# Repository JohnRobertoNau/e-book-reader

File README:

Schema bloc se gaseste aici:
https://drive.google.com/drive/u/0/folders/1svHynGlwr7JKA02n5Jt7F-PYmH98pda1

BOM:

| Component                   | Quantity | Price (€) | Link                                                                                                                            | Datasheet                                                                                                                             |
| :-------------------------- | -------- | --------- | ------------------------------------------------------------------------------------------------------------------------------- | ------------------------------------------------------------------------------------------------------------------------------------- |
| W25Q512JVEIQ                | 1        | 5.84      | https://eu.mouser.com/ProductDetail/Winbond/W25Q512JVEIQ?qs=l7cgNqFNU1jw6svr3at6tA%3D%3D                                        | https://eu.mouser.com/datasheet/2/949/Winbond_W25Q512JV_Datasheet-3240039.pdf                                                         |
| MAX17048G+T10               | 1        | 4.28      | https://eu.mouser.com/ProductDetail/Analog-Devices-Maxim-Integrated/MAX17048G%2bT10?qs=D7PJwyCwLAoGnnn8jEPRBQ%3D%3D             | https://eu.mouser.com/datasheet/2/609/MAX17048_MAX17049-3469099.pdf                                                                   |
| ESP32-C6-WROOM-1-N8         | 1        | 2.97      | https://eu.mouser.com/ProductDetail/Espressif-Systems/ESP32-C6-WROOM-1-N8?qs=8Wlm6%252BaMh8ST02Gmwp74cw%3D%3D                   | https://eu.mouser.com/datasheet/2/891/Espressif_ESP32_C6_WROOM_1__Datasheet_V0_1_PRELIMI-3239987.pdf                                  |
| 112A-TAAR-R03_ATTEND        | 1        | 1.05      | https://store.comet.srl.ro/Catalogue/Product/43497/                                                                             | https://store.comet.bg/download-file.php?id=27596                                                                                     |
| QWIIC_RIGHT_ANGLE           | 1        | 3.75      | https://eu.mouser.com/ProductDetail/Adafruit/4208?qs=PzGy0jfpSMtbScLbr0L5dw%3D%3D                                               | https://cdn-shop.adafruit.com/datasheets/HX8340-B_N__DS_preliminary_v01_071203.pdf                                                    |
| BD5229G-TR                  | 1        | 0.75      | https://eu.mouser.com/ProductDetail/ROHM-Semiconductor/BD5229G-TR?qs=4kLU8WoGk0vvnhrrYwdszw%3D%3D                               | https://fscdn.rohm.com/en/products/databook/datasheet/ic/power/voltage_detector/bd52xxg-e.pdf                                         |
| 1uF capacitor               | 1        | 0.13      | https://eu.mouser.com/ProductDetail/TAIYO-YUDEN/MAASL105CC7105MFCA01?qs=HFfMDpzxxd1Fn%2FInbJA7vw%3D%3D                          | https://eu.mouser.com/datasheet/2/396/TAIYO_YUDEN_04_27_2024_c_mlcc_A_e1-3451516.pdf                                                  |
| PGB1010603MR                | 6        | 0.40      | https://eu.mouser.com/ProductDetail/Littelfuse/PGB1010603MR?qs=gu7KAQ731URLg4GSnNNN7Q%3D%3D                                     | https://www.littelfuse.com/assetdocs/pulseguard-esd-suppressors-pgb1-datasheet?assetguid=8a337998-d54d-466b-be4e-dc5bcd1f9321         |
| MCP73831                    | 1        | 0.16      | https://eu.mouser.com/ProductDetail/Microchip-Technology/MCP73831T-5ACI-OT?qs=hH%252BOa0VZEiAcgAcEkuamXg%3D%3D                  | https://eu.mouser.com/datasheet/2/268/MCP73831_Family_Data_Sheet_DS20001984H-3441711.pdf                                              |
| 200 ohm resistor            | 1        | 0.10      | https://eu.mouser.com/ProductDetail/Wurth-Elektronik/560112110211?qs=sGAEpiMZZMtlubZbdhIBIIgWRUA0vTGpVUEy0IEGMjk%3D             | https://www.we-online.com/components/products/datasheet/560112110211.pdf                                                              |
| 2k ohm resistor             | 1        | 0.57      | https://eu.mouser.com/ProductDetail/Vishay-Beyschlag/MCS04020D2321BE100?qs=sGAEpiMZZMtlubZbdhIBINHXX5XJLWKoe%2FyX%252BeuBVuo%3D | https://www.vishay.com/docs/28700/mcx0x0xpre.pdf                                                                                      |
| XC6220A331MR-G              | 1        | 1.46      | https://eu.mouser.com/ProductDetail/Torex-Semiconductor/XC6220A331MR-G?qs=AsjdqWjXhJ8ZSWznL1J0gg%3D%3D                          | https://eu.mouser.com/datasheet/2/760/xc6220-3371556.pdf                                                                              |
| 100uF tant capacitor        | 1        | 25.19     | https://eu.mouser.com/ProductDetail/Vishay-Sprague/T97F107M035HAA?qs=kE1vTINknaW2TSWjulhndg%3D%3D                               | https://www.vishay.com/docs/40092/t97.pdf                                                                                             |
| 100k resistor               | 1        | 0.30      | https://eu.mouser.com/ProductDetail/Vishay-BC-Components/NTCS0402E3104JHT?qs=8wHch9UpSvY0bmpK2FbGWQ%3D%3D                       | https://www.vishay.com/docs/29003/ntcs0402e3t.pdf                                                                                     |
| CPH3225A                    | 1        | 2.33      | https://eu.mouser.com/ProductDetail/Seiko-Semiconductors/CPH3225A?qs=3etwrb1wR%252BhUOph6lAO7eg%3D%3D                           | https://eu.mouser.com/datasheet/2/360/Seiko_Instruments_MicroBattery_E_20230330_2024Jan_-3561061.pdf                                  |
| R_CAPACITOR                 | 1        | 0.12      | https://eu.mouser.com/ProductDetail/Panasonic/ERJ-2RKD15R0X?qs=8CJXEYeWfIrWZI67d3moiA%3D%3D                                     | https://industrial.panasonic.com/cdbs/www-data/pdf/RDA0000/AOA0000C304.pdf                                                            |
| FH34SRJ-24S-0.5SH_99_       | 1        | 2.60      | https://eu.mouser.com/ProductDetail/Hirose-Connector/FH34SRJ-24S-0.5SH99?qs=vcbW%252B4%252BSTIpKBl5ap9J8Fw%3D%3D                | https://eu.mouser.com/datasheet/2/185/FH34SRJ_24S_0_5SH_99__CL0580_1255_6_99_2DDrawing_0-1615044.pdf                                  |
| 0.1uF/50V capacitor         | 1        | 0.45      | https://eu.mouser.com/ProductDetail/KYOCERA-AVX/04025C104MAT2A?qs=sGAEpiMZZMukHu%252BjC5l7YbsWA2wxb4GLrh7pRRirNkk%3D            | https://eu.mouser.com/datasheet/2/40/KGM_X7R-3223212.pdf                                                                              |
| 1uF/50V capacitor           | 10       | 0.56      | https://eu.mouser.com/ProductDetail/TAIYO-YUDEN/MAASU32NSB7105KTCA01?qs=HFfMDpzxxd06eur8w0VYhA%3D%3D                            | https://eu.mouser.com/datasheet/2/396/TDK_4_24_2024_MAASU32NSB7105KTCA01_SS-3440852.pdf                                               |
| 2k ohm resistor             | 1        | 0.57      | https://eu.mouser.com/ProductDetail/Vishay-Beyschlag/MCS04020D2321BE100?qs=sGAEpiMZZMtlubZbdhIBINHXX5XJLWKoe%2FyX%252BeuBVuo%3D | https://www.vishay.com/docs/28700/mcx0x0xpre.pdf                                                                                      |
| BME688                      | 1        | 14.82     | https://eu.mouser.com/ProductDetail/Bosch-Sensortec/BME680-Shuttle-Board-3.0?qs=Wj%2FVkw3K%252BMABg5lm5143Ww%3D%3D              | https://eu.mouser.com/datasheet/2/783/bst_bme680_sf000-2486508.pdf                                                                    |
| 2.2 ohm resistor            | 1        | 0.15      | https://eu.mouser.com/ProductDetail/Panasonic/ERJ-PA2J2R2X?qs=sGAEpiMZZMtlubZbdhIBIKn8wLs5z3UnO%252BN6Zqj8Y2A%3D                | https://industrial.panasonic.com/cdbs/www-data/pdf/RDO0000/AOA0000C331.pdf                                                            |
| MBR0530                     | 3        | 0.18      | https://eu.mouser.com/ProductDetail/onsemi/MBR0530T3G?qs=3JMERSakebpEmdUS6GetdQ%3D%3D                                           | https://www.onsemi.com/download/data-sheet/pdf/mbr0530t1-d.pdf                                                                        |
| SI1308EDL-T1-GE3            | 1        | 0.42      | https://eu.mouser.com/ProductDetail/Vishay-Semiconductors/SI1308EDL-T1-GE3?qs=bX1%252BNvsK%2FBramh9tgpOaEw%3D%3D                | https://www.vishay.com/docs/63399/si1308edl.pdf                                                                                       |
| 0.47 ohm resistor           | 1        | 0.61      | https://eu.mouser.com/ProductDetail/ROHM-Semiconductor/UCR01MVPFLR470?qs=493kPxzlxfJor42A3tTE6g%3D%3D                           | https://fscdn.rohm.com/en/products/databook/datasheet/passive/resistor/chip_resistor/ucr-e.pdf                                        |
| 4.7uF/25V capacitor         | 1        | 0.27      | https://eu.mouser.com/ProductDetail/KYOCERA-AVX/04023D475MAT2A?qs=sGAEpiMZZMsh%252B1woXyUXj%252BCoURFk43JpehNp%2F1Fl9pk%3D      | https://eu.mouser.com/datasheet/2/40/cx5r-2835979.pdf                                                                                 |
| 68uH ind                    | 1        | 1.37      | https://store.comet.srl.ro/CatalogueFarnell/Product/1302649/                                                                    | https://www.we-online.com/components/products/datasheet/744043680.pdf                                                                 |
| 10uF capacitor              | 1        | 0.28      | https://eu.mouser.com/ProductDetail/KYOCERA-AVX/KGM05CS60J106MH?qs=9vOqFld9vZXSfhl2b2Q2gQ%3D%3D                                 | https://eu.mouser.com/datasheet/2/40/KGM_X6S-3223173.pdf                                                                              |
| SAMACSYS_PARTS_USB4110-GF-A | 1        | 1.18      | https://eu.mouser.com/ProductDetail/GCT/USB4110-GF-A?qs=KUoIvG%2F9IlYiZvIXQjyJeA%3D%3D                                          | https://eu.mouser.com/datasheet/2/837/GCT_USB4110_Product_Drawing___20k_cycles-3455479.pdf                                            |
| PFMF.050.1                  | 1        | 0.28      | https://eu.mouser.com/ProductDetail/Schurter/PFMF.050.2?qs=1auRipcfynCums5v1iucSA%3D%3D                                         | https://eu.mouser.com/datasheet/2/358/typ_PFMF-1275918.pdf                                                                            |
| 5k1 resistor                | 2        | 0.15      | https://eu.mouser.com/ProductDetail/Vishay-Beyschlag/MCS04020C5101FE000?qs=sGAEpiMZZMtlubZbdhIBIMAhWB6%252BRofmP3o4x7R7qwI%3D   | https://www.vishay.com/docs/28705/mcx0x0xpro.pdf                                                                                      |
| Battery                     | 1        | 10.45     | https://www.emag.ro/acumulator-li-polymer-2500mah-3-7v-104050-243/pd/D6VB6SMBM/                                                 | https://www.ufinebattery.com/images/upload/ufx0165-11-3-7v-2500mah-lithium-ion-battery-product-datasheet.pdf                          |
| Display                     | 1        | 44.12     | https://www.waveshare.com/7.5inch-e-paper.htm                                                                                   | https://files.waveshare.com/upload/6/60/7.5inch_e-Paper_V2_Specification.pdf                                                          |
| 100nF capacitor             | 8        | 0.013     | https://store.comet.srl.ro/Catalogue/Product/48939/                                                                             | https://store.comet.bg/download-file.php?id=11                                                                                        |
| 10k resistor                | 16       | 0.19      | https://eu.mouser.com/ProductDetail/Vishay/MCS04020D1022BE000?qs=pUKx8fyJudATYWOpd0Fc%2FA%3D%3D                                 | https://www.vishay.com/docs/28700/mcx0x0xpre.pdf                                                                                      |
| 4.7uF capacitor             | 5        | 0.82      | https://eu.mouser.com/ProductDetail/KEMET/C0402C475K8PACTU?qs=sGAEpiMZZMsh%252B1woXyUXj%252BeMYF%2FJh1ZHWLnD7xub%252BoY%3D      | https://eu.mouser.com/datasheet/2/447/KEM_C1006_X5R_SMD-3316465.pdf                                                                   |
| SD0805S020S1R0              | 2        | 0.30      | https://eu.mouser.com/ProductDetail/KYOCERA-AVX/SD0805S020S1R0?qs=jCA%252BPfw4LHbpkAoSnwrdjw%3D%3D                              | https://eu.mouser.com/ProductDetail/KYOCERA-AVX/SD0805S020S1R0?qs=jCA%252BPfw4LHbpkAoSnwrdjw%3D%3D                                    |
| DMG2305UX-7                 | 2        | 0.2       | https://store.comet.srl.ro/CatalogueFarnell/Product/1773598/                                                                    | https://4donline.ihs.com/images/VipMasterIC/IC/DIOD/DIOD-S-A0013043571/DIOD-S-A0013120650-1.pdf?hkey=6D3A4C79FDBF58556ACFDE234799DDF0 |

-------------------------------------------------------------------------------
Examinare 3D a dispozitivului:
 - pentru a vedea in Fusion ce este in spatele ecranului:
    apasa Hide pe Browser -> Bodies -> Box: vei vedea placuta si bateria

- Sketch 43 reprezinta bateria
- Sketch 44 reprezinta ecranul
- Pentru a vedea imagini cu dispozitivul cauta in directorul Images al acestui
repository

-------------------------------------------------------------------------------
Descriere Proiect:

OpenBook este un e-book reader open-source implementat pentru o citire simpla a
cartilor electronice. Pentru elaborarea acestui proiect au fost folosite
componente din biblioteca deskassistant. Erorile au fost verificate cu ajutorul
unui fisier de tip ".drc". Principala componenta este un microcontroller
ESP32-C6. Intregului dispozititv ii este asociat o baterie si un ecran, toate
acestea fiind amplasate intr-o carcasa, fiind vizibile in directorul Mechanical

-------------------------------------------------------------------------------
Componente Hardware folosite:
- ESP32-C6: Microcontroller principal, care asigura conectivitatea si
procesarea datelor.
- E-Paper Display: Display cu consum redus de energie, conectat prin
interfața SPI.
- Senzor de Mediu BME688: Masoara parametrii de mediu și trimite date
prin interfața I2C.
- Memorie NOR Flash 64MB: Stocare extensibila pentru fișiere de e-book.
- Modul RTC DS3231SN: Ofera funcționalitate de ceas în timp real.
- Conector USB-C: Incarcare și transfer de date.
- Baterie Li-Po: Alimentare principala a dispozitivului.
- Conectori pentru SD Card: Pentru extinderea memoriei si stocarea cartilor.

-------------------------------------------------------------------------------
ESP32-C6:
 - GPIO pinii sunt utilizați pentru conectarea senzorilor și a altor componente periferice.
 - SPI pentru E-Paper și memorie Flash.
 - I2C pentru senzorul de mediu.

Interfețe principale:
 - SPI: Conecteaza ecranul E-Paper și memoria Flash.
 - I2C: Conectează senzorul BME688 și modulul RTC.
 - UART: Pentru comunicație seriala.

Pini Utilizați - ESP32-C6:
 - GPIO16: TX pentru comunicație serială.
 - GPIO17: RX pentru comunicație serială.
 - GPIO21: SDA pentru I2C.
 - GPIO22: SCL pentru I2C.
 - GPIO18, GPIO19: SCK și MISO pentru SPI.
 - GPIO5: Chip Select pentru memorie Flash.
 - GPIO4: Reset pentru E-Paper.

 ------------------------------------------------------------------------------
 Probleme si gestionarea erorilor:

  - A fost necesara aprobarea a 2 erori de tip "smd-hole", deoarece piesa
  pentru J3 era defecta.
  - Pentru TP-uri a trebuit sa implementez propriul design.
  - Folosirea de VIAS-uri pentru a evita intersectia cablurilor.

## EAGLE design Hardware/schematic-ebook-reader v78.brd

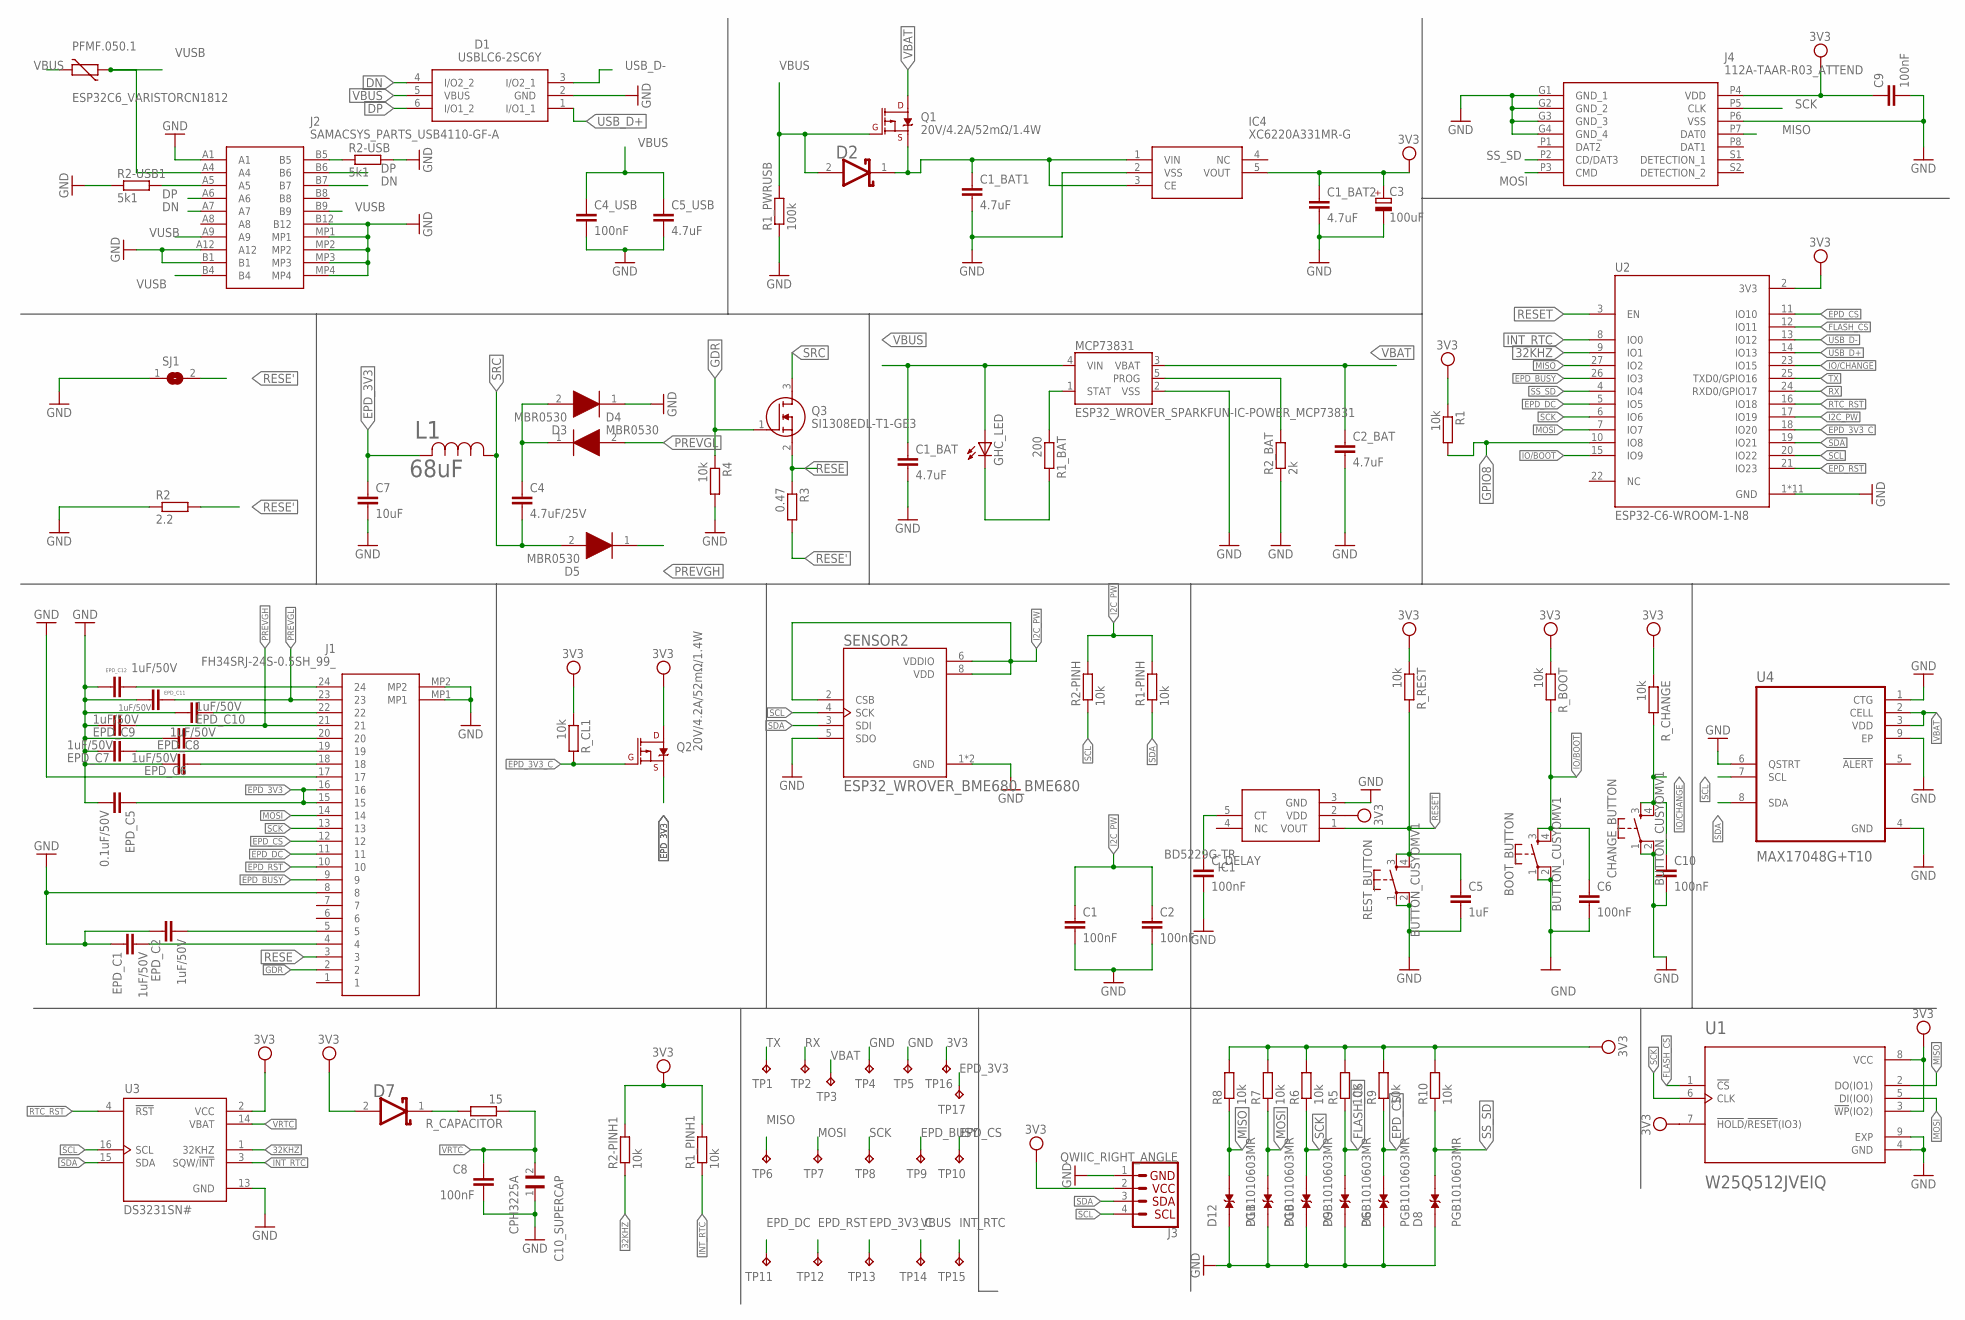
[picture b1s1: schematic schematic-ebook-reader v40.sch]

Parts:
BOOT_BUTTON: BUTTON_CUSYOMV1; MYBUTTON
C1, C2, C4_USB, C6, C8, C9, C10: 100nF; ESP32_WROVER_EAGLE-LTSPICE_C0402
C1_BAT, C1_BAT1, C1_BAT2, C2_BAT, C5_USB: 4.7uF; ESP32_WROVER_EAGLE-LTSPICE_C0402
C3: 100uF; RCL_CT3528
C4: 4.7uF/25V; ESP32_WROVER_EAGLE-LTSPICE_C0402
C5: 1uF; ESP32_WROVER_EAGLE-LTSPICE_C0402
C7: 10uF; ESP32_WROVER_EAGLE-LTSPICE_C0402
C10_SUPERCAP: CPH3225A; CAPCP3225X100N
CHANGE_BUTTON: BUTTON_CUSYOMV1; MYBUTTON
C_DELAY: 100nF; ESP32_WROVER_EAGLE-LTSPICE_C0402
D1: USBLC6-2SC6Y; SOT95P280X145-6N
D2, D7: ESP32_WROVER_AVX---SD0805S020S1R0_AVX_SD0805S020S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; ESP32_WROVER_AVX---SD0805S020S1R0_AVX_SD0805S020S1R0_0
D3, D4, D5: MBR0530; SOD3716X135N
D6, D8, D9, D10, D11, D12: PGB1010603MR; DIOC1608X36N
EPD_C1, EPD_C2, EPD_C6, EPD_C7, EPD_C8, EPD_C9, EPD_C10, EPD_C11, EPD_C12: 1uF/50V; ESP32_WROVER_EAGLE-LTSPICE_C0402
EPD_C5: 0.1uF/50V; ESP32_WROVER_EAGLE-LTSPICE_C0402
GHC_LED: ADAFRUIT_LEDCHIP-LED0603; ADAFRUIT_CHIP-LED0603
IC1: BD5229G-TR; SOT95P280X125-5N
IC4: XC6220A331MR-G; SOT95P280X120-5N
J1: FH34SRJ-24S-0.5SH_99_; FH34SRJ24S05SH99
J2: SAMACSYS_PARTS_USB4110-GF-A; SAMACSYS_PARTS_USB4110GFA
J3: QWIIC_RIGHT_ANGLE; JST04_1MM_RA
J4: 112A-TAAR-R03_ATTEND; 112ATAARR03ATTEND
L1: 68uF; IND_4828-WE-TPC_WRE
MCP73831: ESP32_WROVER_SPARKFUN-IC-POWER_MCP73831; ESP32_WROVER_SPARKFUN-IC-POWER_SOT23-5
PFMF.050.1: ESP32C6_VARISTORCN1812; ESP32C6_VARISTOR_CT/CN1812
Q1, Q2: 20V/4.2A/52mΩ/1.4W; ESP32_WROVER_SPARKFUN-DISCRETESEMI_SOT23-3
Q3: SI1308EDL-T1-GE3; SOT65P210X110-3N
R1, R1-PINH, R1_PINH1, R2-PINH, R2-PINH1, R4, R5, R6, R7, R8, R9, R10: 10k; ESP32_WROVER_EAGLE-LTSPICE_C0402
R1_BAT: 200; ESP32_WROVER_EAGLE-LTSPICE_C0402
R1_PWRUSB: 100k; ESP32_WROVER_EAGLE-LTSPICE_C0402
R2: 2.2; ESP32_WROVER_EAGLE-LTSPICE_C0402
R2-USB, R2-USB1: 5k1; ESP32_WROVER_EAGLE-LTSPICE_C0402
R2_BAT: 2k; ESP32_WROVER_EAGLE-LTSPICE_C0402
R3: 0.47; ESP32_WROVER_EAGLE-LTSPICE_C0402
REST_BUTTON: BUTTON_CUSYOMV1; MYBUTTON
R_BOOT: 10k; ESP32_WROVER_EAGLE-LTSPICE_C0402
R_CAPACITOR: 15; ESP32_WROVER_EAGLE-LTSPICE_C0402
R_CHANGE: 10k; ESP32_WROVER_EAGLE-LTSPICE_C0402
R_CL1: 10k; ESP32_WROVER_EAGLE-LTSPICE_C0402
R_REST: 10k; ESP32_WROVER_EAGLE-LTSPICE_C0402
SENSOR2: ESP32_WROVER_BME680_BME680; ESP32_WROVER_BME680_PSON80P300X300X100-8N
SJ1: SJ
TP1, TP2, TP3, TP4, TP5, TP6, TP7, TP8, TP9, TP10, TP11, TP12, TP13, TP14, TP15, TP16, TP17: TPTP20R; TP20R
U1: W25Q512JVEIQ; SON127P600X800X80-9N
U2: ESP32-C6-WROOM-1-N8; XCVR_ESP32-C6-WROOM-1-N8
U3: DS3231SN#; SOIC127P1032X265-16N
U4: MAX17048G+T10; SON50P200X200X80-9N

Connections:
3V3: C1_BAT2.1, C3.+, C9.1, D7.2 (ANODE), IC1.2 (VDD), IC4.5 (VOUT), J3.2, J4.P4 (VDD), Q2.3 (D), R1.1, R1_PINH1.2, R2-PINH1.2, R5.2, R6.2, R7.2, R8.2, R9.2, R10.2, R_BOOT.1, R_CHANGE.1, R_CL1.1, R_REST.1, TP16.TP, U1.3 (!WP!(IO2)), U1.7 (!HOLD!/!RESET!(IO3)), U1.8 (VCC), U2.2 (3V3), U3.2 (VCC); also elsewhere on the board
32KHZ: R2-PINH1.1, U2.9 (IO1), U3.1 (32KHZ)
DN: D1.4 (I/O2_2), J2.A7, J2.B7
DP: D1.6 (I/O1_2), J2.A6, J2.B6
EPD_3V3: C7.1, EPD_C5.1, J1.15, J1.16, L1.2, Q2.2 (S), TP17.TP
EPD_3V3_C: Q2.1 (G), R_CL1.2, TP13.TP, U2.18 (IO20)
EPD_BUSY: J1.9, TP9.TP, U2.26 (IO3)
EPD_CS: D6.2, J1.12, R9.1, TP10.TP, U2.11 (IO10)
EPD_DC: J1.11, TP11.TP, U2.5 (IO5)
EPD_RST: J1.10, TP12.TP, U2.21 (IO23)
FLASH_CS: D9.2, R5.1, U1.1 (!CS), U2.12 (IO11)
GDR: J1.2, Q3.1 (G), R4.1
GND: BOOT_BUTTON.1, BOOT_BUTTON.2, C1.2, C1_BAT.2, C1_BAT1.2, C1_BAT2.2, C2.2, C2_BAT.2, C3.-, C4_USB.2, C5.2, C5_USB.2, C6.2, C7.2, C8.2, C9.2, C10.2, C10_SUPERCAP.1, CHANGE_BUTTON.1, CHANGE_BUTTON.2, C_DELAY.2, D1.2 (GND), D3.1 (K), D6.1, D8.1, D9.1, D10.1, D11.1, D12.1, EPD_C1.1, EPD_C2.1, EPD_C5.2, EPD_C6.2, EPD_C7.2, EPD_C8.2, EPD_C9.2, EPD_C10.2, EPD_C11.2, EPD_C12.2, IC1.3 (GND), IC4.2 (VSS), J1.8, J1.17, J1.MP1, J1.MP2, J2.A1, J2.A12, J2.B1, J2.B12, J2.MP1, J2.MP2, J2.MP3, J2.MP4, J3.1, J4.G1 (GND_1), J4.G2 (GND_2), J4.G3 (GND_3), J4.G4 (GND_4), J4.P6 (VSS), MCP73831.2 (VSS), R1_PWRUSB.1, R2.1, R2-USB.2, R2-USB1.1, R2_BAT.1, R4.2, REST_BUTTON.1, REST_BUTTON.2, SENSOR2.1 (GND), SENSOR2.5 (SDO), SENSOR2.7 (GND), SJ1.1, TP4.TP, TP5.TP, U1.4 (GND), U1.9 (EXP), U2.1 (GND), U2.28 (GND), U2.29_1 (GND), U2.29_2 (GND), U2.29_3 (GND), U2.29_4 (GND), U2.29_5 (GND), U2.29_6 (GND), U2.29_7 (GND), U2.29_8 (GND), U2.29_9 (GND), U3.13 (GND), U4.1 (CTG), U4.4 (GND), U4.6 (QSTRT), U4.9 (EP); also elsewhere on the board
GPIO8: R1.2, U2.10 (IO8)
I2C_PW: C1.1, C2.1, R1-PINH.2, R2-PINH.2, SENSOR2.2 (CSB), SENSOR2.6 (VDDIO), SENSOR2.8 (VDD), U2.17 (IO19)
INT_RTC: R1_PINH1.1, TP15.TP, U2.8 (IO0), U3.3 (SQW/!INT)
IO/BOOT: BOOT_BUTTON.3, BOOT_BUTTON.4, C6.1, R_BOOT.2, U2.15 (IO9)
IO/CHANGE: C10.1, CHANGE_BUTTON.3, CHANGE_BUTTON.4, R_CHANGE.2, U2.23 (IO15)
MISO: D12.2, J4.P7 (DAT0), R8.1, TP6.TP, U1.2 (DO(IO1)), U2.27 (IO2)
MOSI: D11.2, J1.14, J4.P3 (CMD), R7.1, TP7.TP, U1.5 (DI(IO0)), U2.7 (IO7)
unnamed: EPD_C2.2, J1.5
unnamed: J2.A5, R2-USB1.2
unnamed: J2.B5, R2-USB.1
unnamed: C1_BAT1.1, D2.1 (CATHODE), IC4.1 (VIN), IC4.3 (CE), Q1.2 (S)
unnamed: MCP73831.1 (STAT), R1_BAT.1
unnamed: C_DELAY.1, IC1.5 (CT)
unnamed: C4.1, D3.2 (A), D4.1 (K)
unnamed: MCP73831.5 (PROG), R2_BAT.2
unnamed: GHC_LED.C, R1_BAT.2
unnamed: EPD_C10.1, J1.22
unnamed: EPD_C12.1, J1.24
unnamed: EPD_C8.1, J1.20
unnamed: EPD_C7.1, J1.19
unnamed: EPD_C6.1, J1.18
unnamed: D7.1 (CATHODE), R_CAPACITOR.2
unnamed: EPD_C1.2, J1.4
PREVGH: D5.1 (K), EPD_C9.1, J1.21
PREVGL: D4.2 (A), EPD_C11.1, J1.23
RESE: J1.3, Q3.2 (S), R3.1
RESE': R2.2, R3.2, SJ1.2
RESET: C5.1, IC1.1 (VOUT), REST_BUTTON.3, REST_BUTTON.4, R_REST.2, U2.3 (EN); also elsewhere on the board
RTC_RST: U2.16 (IO18), U3.4 (!RST)
RX: TP2.TP, U2.24 (RXD0/GPIO17)
SCK: D10.2, J1.13, J4.P5 (CLK), R6.1, TP8.TP, U1.6 (CLK), U2.6 (IO6)
SCL: J3.4, R2-PINH.1, SENSOR2.4 (SCK), U2.20 (IO22), U3.16 (SCL), U4.7 (SCL)
SDA: J3.3, R1-PINH.1, SENSOR2.3 (SDI), U2.19 (IO21), U3.15 (SDA), U4.8 (SDA)
SRC: C4.2, D5.2 (A), L1.1, Q3.3 (D)
SS_SD: D8.2, J4.P2 (CD/DAT3), R10.1, U2.4 (IO4)
TX: TP1.TP, U2.25 (TXD0/GPIO16)
USB_D+: D1.1 (I/O1_1), U2.14 (IO13)
USB_D-: D1.3 (I/O2_1), U2.13 (IO12)
VBAT: C2_BAT.1, MCP73831.3 (VBAT), Q1.3 (D), TP3.TP, U4.2 (CELL), U4.3 (VDD)
VBUS: C1_BAT.1, C4_USB.1, C5_USB.1, D1.5 (VBUS), D2.2 (ANODE), GHC_LED.A, MCP73831.4 (VIN), PFMF.050.1.2, Q1.1 (G), R1_PWRUSB.2, TP14.TP
VRTC: C8.1, C10_SUPERCAP.2, R_CAPACITOR.1, U3.14 (VBAT)
VUSB: J2.A4, J2.A9, J2.B4, J2.B9, PFMF.050.1.1

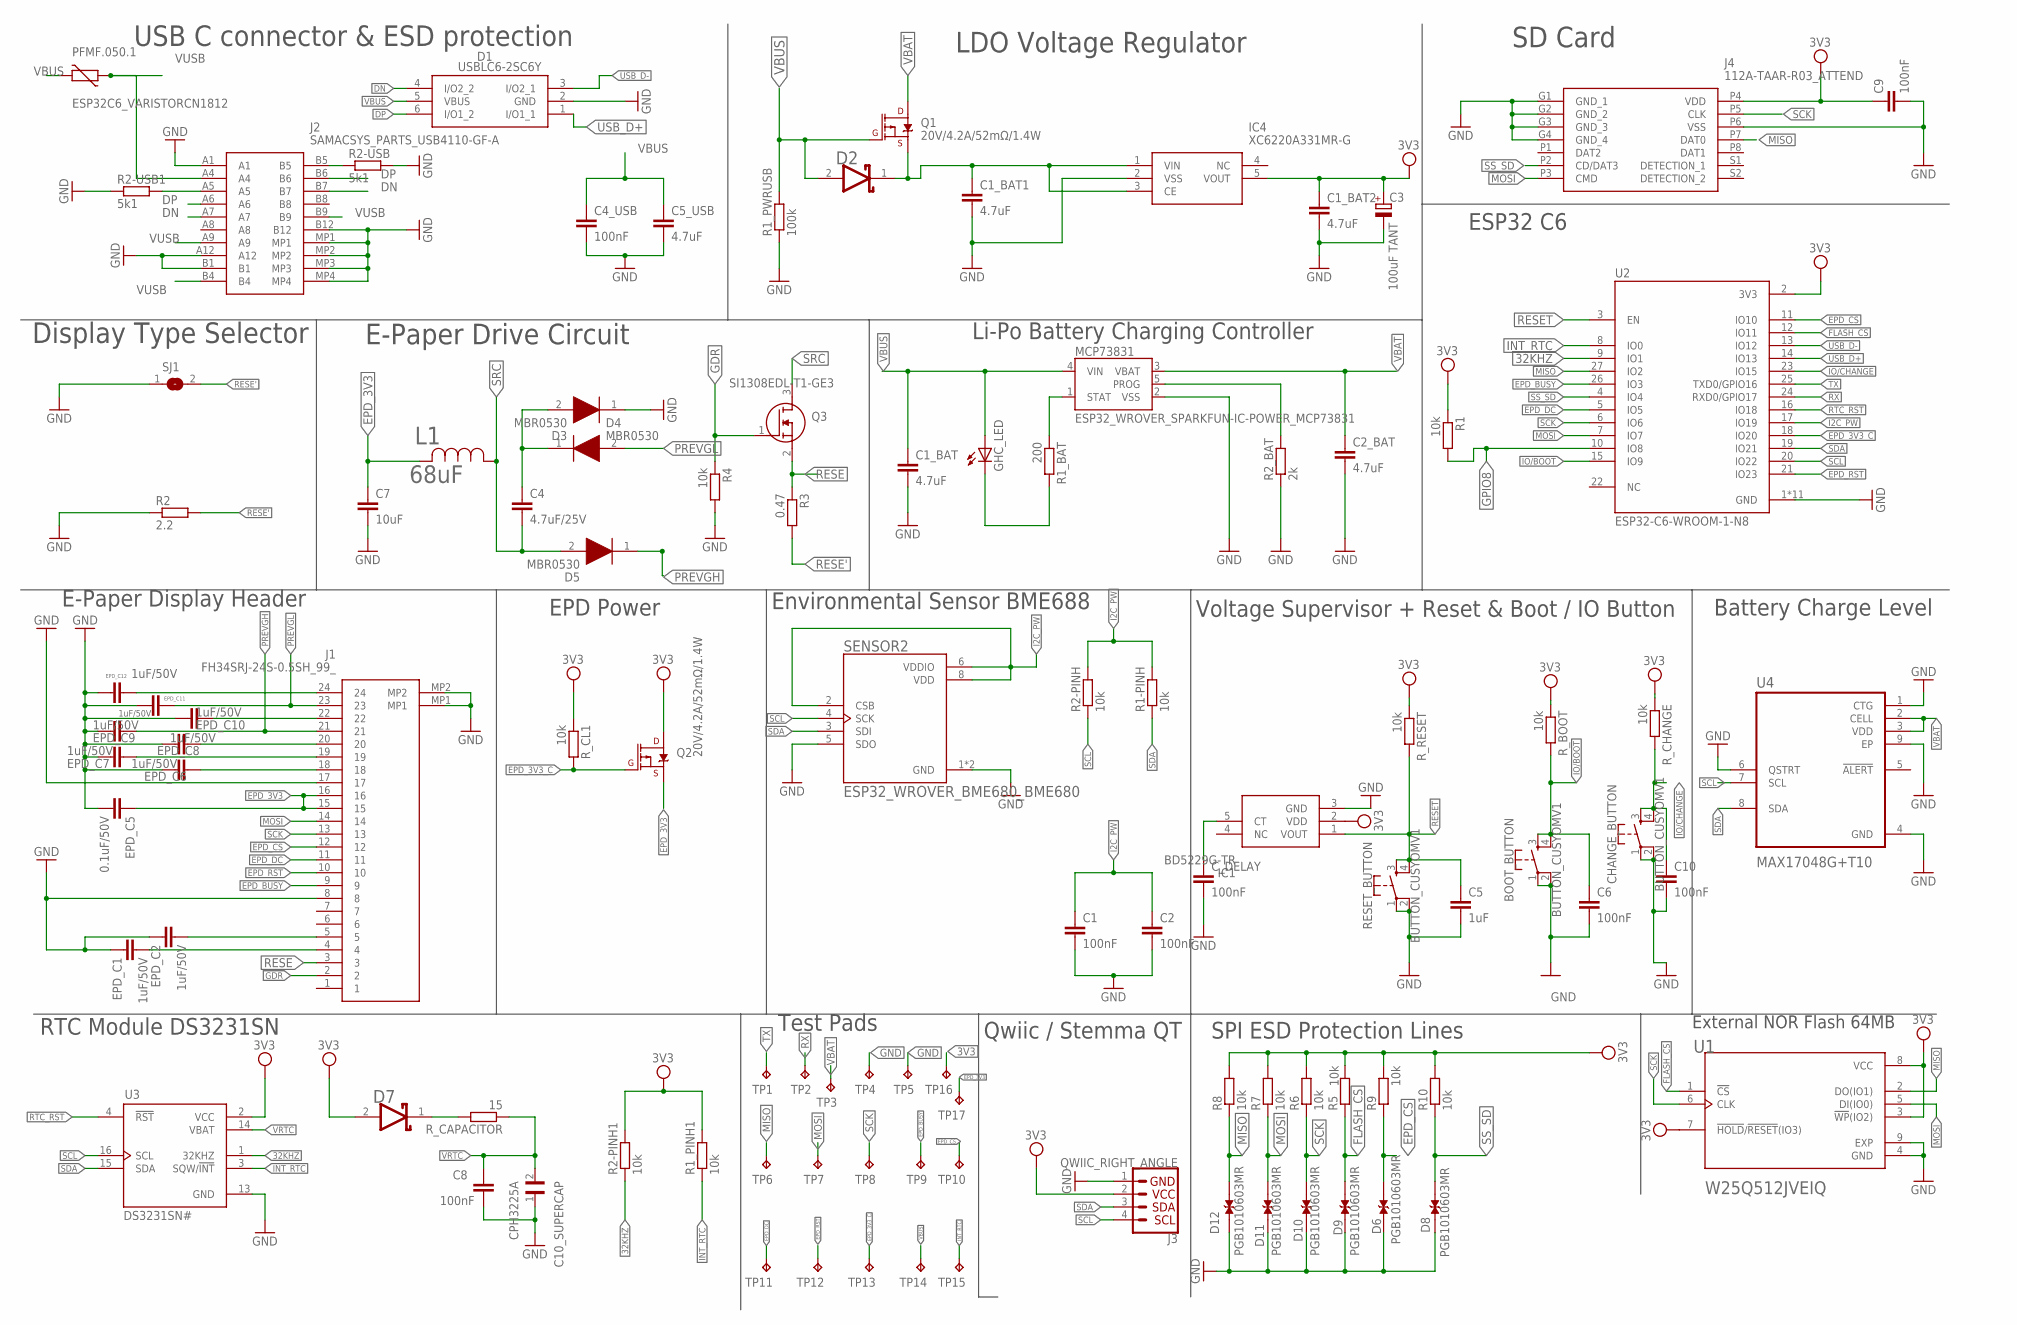
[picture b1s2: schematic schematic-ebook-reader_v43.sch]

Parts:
BOOT_BUTTON: BUTTON_CUSYOMV1; MYBUTTON
C1, C2, C4_USB, C6, C8, C9, C10: 100nF; ESP32_WROVER_EAGLE-LTSPICE_C0402
C1_BAT, C1_BAT1, C1_BAT2, C2_BAT, C5_USB: 4.7uF; ESP32_WROVER_EAGLE-LTSPICE_C0402
C3: 100uF TANT; RCL_CT3528
C4: 4.7uF/25V; ESP32_WROVER_EAGLE-LTSPICE_C0402
C5: 1uF; ESP32_WROVER_EAGLE-LTSPICE_C0402
C7: 10uF; ESP32_WROVER_EAGLE-LTSPICE_C0402
C10_SUPERCAP: CPH3225A; CAPCP3225X100N
CHANGE_BUTTON: BUTTON_CUSYOMV1; MYBUTTON
C_DELAY: 100nF; ESP32_WROVER_EAGLE-LTSPICE_C0402
D1: USBLC6-2SC6Y; SOT95P280X145-6N
D2, D7: ESP32_WROVER_AVX---SD0805S020S1R0_AVX_SD0805S020S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; ESP32_WROVER_AVX---SD0805S020S1R0_AVX_SD0805S020S1R0_0
D3, D4, D5: MBR0530; SOD3716X135N
D6, D8, D9, D10, D11, D12: PGB1010603MR; DIOC1608X36N
EPD_C1, EPD_C2, EPD_C6, EPD_C7, EPD_C8, EPD_C9, EPD_C10, EPD_C11, EPD_C12: 1uF/50V; ESP32_WROVER_EAGLE-LTSPICE_C0402
EPD_C5: 0.1uF/50V; ESP32_WROVER_EAGLE-LTSPICE_C0402
GHC_LED: ADAFRUIT_LEDCHIP-LED0603; ADAFRUIT_CHIP-LED0603
IC1: BD5229G-TR; SOT95P280X125-5N
IC4: XC6220A331MR-G; SOT95P280X120-5N
J1: FH34SRJ-24S-0.5SH_99_; FH34SRJ24S05SH99
J2: SAMACSYS_PARTS_USB4110-GF-A; SAMACSYS_PARTS_USB4110GFA
J3: QWIIC_RIGHT_ANGLE; JST04_1MM_RA
J4: 112A-TAAR-R03_ATTEND; 112ATAARR03ATTEND
L1: 68uF; IND_4828-WE-TPC_WRE
MCP73831: ESP32_WROVER_SPARKFUN-IC-POWER_MCP73831; ESP32_WROVER_SPARKFUN-IC-POWER_SOT23-5
PFMF.050.1: ESP32C6_VARISTORCN1812; ESP32C6_VARISTOR_CT/CN1812
Q1, Q2: 20V/4.2A/52mΩ/1.4W; ESP32_WROVER_SPARKFUN-DISCRETESEMI_SOT23-3
Q3: SI1308EDL-T1-GE3; SOT65P210X110-3N
R1, R1-PINH, R1_PINH1, R2-PINH, R2-PINH1, R4, R5, R6, R7, R8, R9, R10: 10k; ESP32_WROVER_EAGLE-LTSPICE_C0402
R1_BAT: 200; ESP32_WROVER_EAGLE-LTSPICE_C0402
R1_PWRUSB: 100k; ESP32_WROVER_EAGLE-LTSPICE_C0402
R2: 2.2; ESP32_WROVER_EAGLE-LTSPICE_C0402
R2-USB, R2-USB1: 5k1; ESP32_WROVER_EAGLE-LTSPICE_C0402
R2_BAT: 2k; ESP32_WROVER_EAGLE-LTSPICE_C0402
R3: 0.47; ESP32_WROVER_EAGLE-LTSPICE_C0402
RESET_BUTTON: BUTTON_CUSYOMV1; MYBUTTON
R_BOOT: 10k; ESP32_WROVER_EAGLE-LTSPICE_C0402
R_CAPACITOR: 15; ESP32_WROVER_EAGLE-LTSPICE_C0402
R_CHANGE: 10k; ESP32_WROVER_EAGLE-LTSPICE_C0402
R_CL1: 10k; ESP32_WROVER_EAGLE-LTSPICE_C0402
R_RESET: 10k; ESP32_WROVER_EAGLE-LTSPICE_C0402
SENSOR2: ESP32_WROVER_BME680_BME680; ESP32_WROVER_BME680_PSON80P300X300X100-8N
SJ1: SJ
TP1, TP2, TP3, TP4, TP5, TP6, TP7, TP8, TP9, TP10, TP11, TP12, TP13, TP14, TP15, TP16, TP17: TPTP20R; TP20R
U1: W25Q512JVEIQ; SON127P600X800X80-9N
U2: ESP32-C6-WROOM-1-N8; XCVR_ESP32-C6-WROOM-1-N8
U3: DS3231SN#; SOIC127P1032X265-16N
U4: MAX17048G+T10; SON50P200X200X80-9N

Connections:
3V3: C1_BAT2.1, C3.+, C9.1, D7.2 (ANODE), IC1.2 (VDD), IC4.5 (VOUT), J3.2, J4.P4 (VDD), Q2.3 (D), R1.1, R1_PINH1.2, R2-PINH1.2, R5.2, R6.2, R7.2, R8.2, R9.2, R10.2, R_BOOT.1, R_CHANGE.1, R_CL1.1, R_RESET.1, TP16.TP, U1.3 (!WP!(IO2)), U1.7 (!HOLD!/!RESET!(IO3)), U1.8 (VCC), U2.2 (3V3), U3.2 (VCC); also elsewhere on the board
32KHZ: R2-PINH1.1, U2.9 (IO1), U3.1 (32KHZ)
DN: D1.4 (I/O2_2), J2.A7, J2.B7
DP: D1.6 (I/O1_2), J2.A6, J2.B6
EPD_3V3: C7.1, EPD_C5.1, J1.15, J1.16, L1.2, Q2.2 (S), TP17.TP
EPD_3V3_C: Q2.1 (G), R_CL1.2, TP13.TP, U2.18 (IO20)
EPD_BUSY: J1.9, TP9.TP, U2.26 (IO3)
EPD_CS: D6.2, J1.12, R9.1, TP10.TP, U2.11 (IO10)
EPD_DC: J1.11, TP11.TP, U2.5 (IO5)
EPD_RST: J1.10, TP12.TP, U2.21 (IO23)
FLASH_CS: D9.2, R5.1, U1.1 (!CS), U2.12 (IO11)
GDR: J1.2, Q3.1 (G), R4.1
GND: BOOT_BUTTON.1, BOOT_BUTTON.2, C1.2, C1_BAT.2, C1_BAT1.2, C1_BAT2.2, C2.2, C2_BAT.2, C3.-, C4_USB.2, C5.2, C5_USB.2, C6.2, C7.2, C8.2, C9.2, C10.2, C10_SUPERCAP.1, CHANGE_BUTTON.1, CHANGE_BUTTON.2, C_DELAY.2, D1.2 (GND), D3.1 (K), D6.1, D8.1, D9.1, D10.1, D11.1, D12.1, EPD_C1.1, EPD_C2.1, EPD_C5.2, EPD_C6.2, EPD_C7.2, EPD_C8.2, EPD_C9.2, EPD_C10.2, EPD_C11.2, EPD_C12.2, IC1.3 (GND), IC4.2 (VSS), J1.8, J1.17, J1.MP1, J1.MP2, J2.A1, J2.A12, J2.B1, J2.B12, J2.MP1, J2.MP2, J2.MP3, J2.MP4, J3.1, J4.G1 (GND_1), J4.G2 (GND_2), J4.G3 (GND_3), J4.G4 (GND_4), J4.P6 (VSS), MCP73831.2 (VSS), R1_PWRUSB.1, R2.1, R2-USB.2, R2-USB1.1, R2_BAT.1, R4.2, RESET_BUTTON.1, RESET_BUTTON.2, SENSOR2.1 (GND), SENSOR2.5 (SDO), SENSOR2.7 (GND), SJ1.1, TP4.TP, TP5.TP, U1.4 (GND), U1.9 (EXP), U2.1 (GND), U2.28 (GND), U2.29_1 (GND), U2.29_2 (GND), U2.29_3 (GND), U2.29_4 (GND), U2.29_5 (GND), U2.29_6 (GND), U2.29_7 (GND), U2.29_8 (GND), U2.29_9 (GND), U3.13 (GND), U4.1 (CTG), U4.4 (GND), U4.6 (QSTRT), U4.9 (EP); also elsewhere on the board
GPIO8: R1.2, U2.10 (IO8)
I2C_PW: C1.1, C2.1, R1-PINH.2, R2-PINH.2, SENSOR2.2 (CSB), SENSOR2.6 (VDDIO), SENSOR2.8 (VDD), U2.17 (IO19)
INT_RTC: R1_PINH1.1, TP15.TP, U2.8 (IO0), U3.3 (SQW/!INT)
IO/BOOT: BOOT_BUTTON.3, BOOT_BUTTON.4, C6.1, R_BOOT.2, U2.15 (IO9)
IO/CHANGE: C10.1, CHANGE_BUTTON.3, CHANGE_BUTTON.4, R_CHANGE.2, U2.23 (IO15)
MISO: D12.2, J4.P7 (DAT0), R8.1, TP6.TP, U1.2 (DO(IO1)), U2.27 (IO2)
MOSI: D11.2, J1.14, J4.P3 (CMD), R7.1, TP7.TP, U1.5 (DI(IO0)), U2.7 (IO7)
unnamed: EPD_C2.2, J1.5
unnamed: J2.A5, R2-USB1.2
unnamed: J2.B5, R2-USB.1
unnamed: C1_BAT1.1, D2.1 (CATHODE), IC4.1 (VIN), IC4.3 (CE), Q1.2 (S)
unnamed: MCP73831.1 (STAT), R1_BAT.1
unnamed: C_DELAY.1, IC1.5 (CT)
unnamed: C4.1, D3.2 (A), D4.1 (K)
unnamed: MCP73831.5 (PROG), R2_BAT.2
unnamed: GHC_LED.C, R1_BAT.2
unnamed: EPD_C10.1, J1.22
unnamed: EPD_C12.1, J1.24
unnamed: EPD_C8.1, J1.20
unnamed: EPD_C7.1, J1.19
unnamed: EPD_C6.1, J1.18
unnamed: D7.1 (CATHODE), R_CAPACITOR.2
unnamed: EPD_C1.2, J1.4
PREVGH: D5.1 (K), EPD_C9.1, J1.21
PREVGL: D4.2 (A), EPD_C11.1, J1.23
RESE: J1.3, Q3.2 (S), R3.1
RESE': R2.2, R3.2, SJ1.2
RESET: C5.1, IC1.1 (VOUT), RESET_BUTTON.3, RESET_BUTTON.4, R_RESET.2, U2.3 (EN); also elsewhere on the board
RTC_RST: U2.16 (IO18), U3.4 (!RST)
RX: TP2.TP, U2.24 (RXD0/GPIO17)
SCK: D10.2, J1.13, J4.P5 (CLK), R6.1, TP8.TP, U1.6 (CLK), U2.6 (IO6)
SCL: J3.4, R2-PINH.1, SENSOR2.4 (SCK), U2.20 (IO22), U3.16 (SCL), U4.7 (SCL)
SDA: J3.3, R1-PINH.1, SENSOR2.3 (SDI), U2.19 (IO21), U3.15 (SDA), U4.8 (SDA)
SRC: C4.2, D5.2 (A), L1.1, Q3.3 (D)
SS_SD: D8.2, J4.P2 (CD/DAT3), R10.1, U2.4 (IO4)
TX: TP1.TP, U2.25 (TXD0/GPIO16)
USB_D+: D1.1 (I/O1_1), U2.14 (IO13)
USB_D-: D1.3 (I/O2_1), U2.13 (IO12)
VBAT: C2_BAT.1, MCP73831.3 (VBAT), Q1.3 (D), TP3.TP, U4.2 (CELL), U4.3 (VDD)
VBUS: C1_BAT.1, C4_USB.1, C5_USB.1, D1.5 (VBUS), D2.2 (ANODE), GHC_LED.A, MCP73831.4 (VIN), PFMF.050.1.2, Q1.1 (G), R1_PWRUSB.2, TP14.TP
VRTC: C8.1, C10_SUPERCAP.2, R_CAPACITOR.1, U3.14 (VBAT)
VUSB: J2.A4, J2.A9, J2.B4, J2.B9, PFMF.050.1.1

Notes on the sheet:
USB C connector & ESD protection
LDO Voltage Regulator
SD Card
Display Type Selector
E-Paper Drive Circuit
Li-Po Battery Charging Controller
ESP32 C6
E-Paper Display Header
EPD Power
Environmental Sensor BME688
Voltage Supervisor + Reset & Boot / IO Button
Battery Charge Level
RTC Module DS3231SN
Test Pads
Qwiic / Stemma QT
SPI ESD Protection Lines
External NOR Flash 64MB

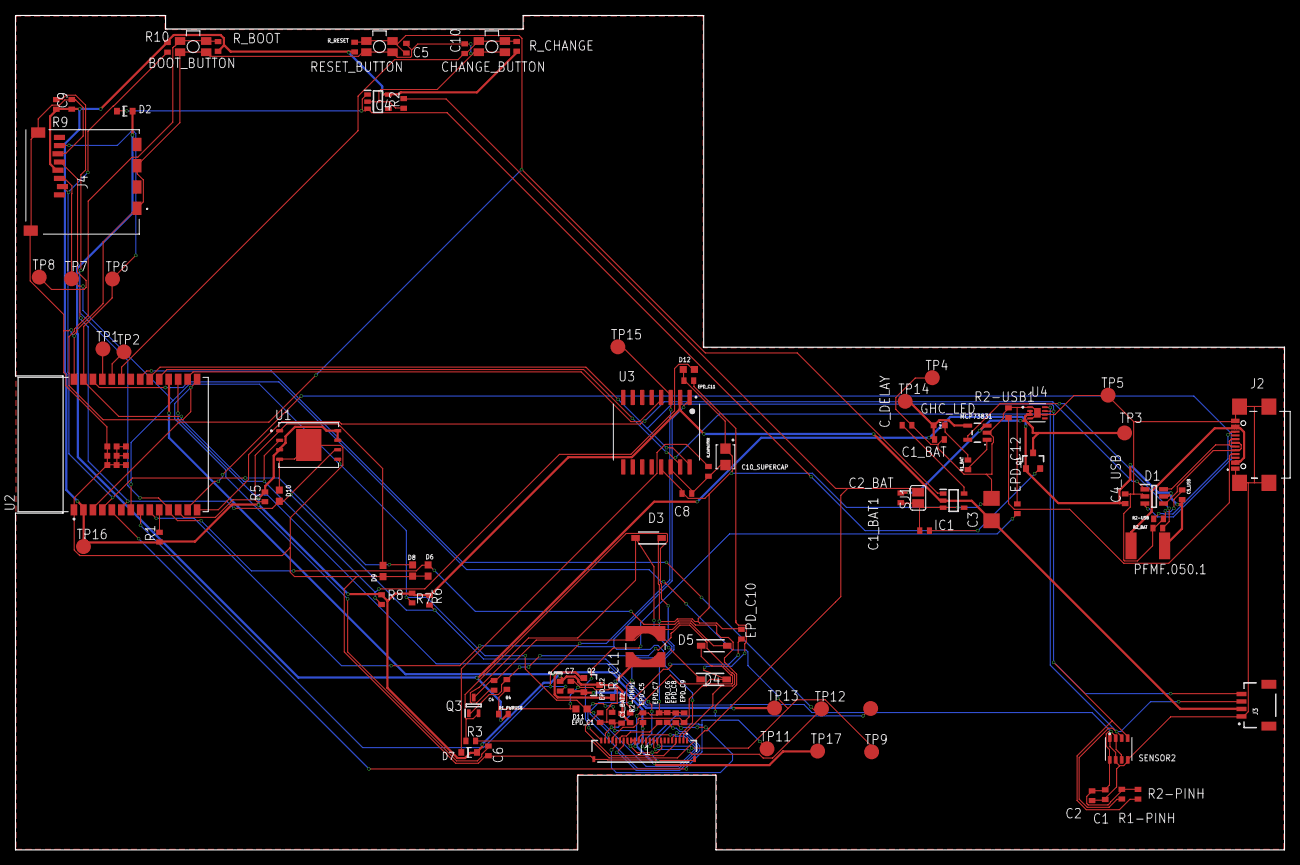
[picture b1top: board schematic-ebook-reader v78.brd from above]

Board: 2 copper layers, 170.1 x 111.8 mm, 103 parts (0 on the bottom side), 55 nets.

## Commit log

2025-04-01 Add files via upload
    16-wire-errors
2025-04-06 proiect final
2025-04-06 Create LICENSE
2025-04-13 Actualizare finala
2025-04-15 DONE
2025-04-15 readme-done-1

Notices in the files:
parts and their libraries:
DeskAssistant v19 v1: COPYRIGHT: Copyright (C) 2024 Ultra Librarian. All rights reserved.
